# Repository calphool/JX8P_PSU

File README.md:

# JX8P_PSU
Replacement power supply for Roland JX8P

The power supply for the Roland JX8P is nearly 40 years old at this point, and if you own a JX8P you should probably be a little concerned about its 
typical manner of failing, which is to spike the +5V rail (your logic rail) frying lots of logic chips on your synth.  It is also built 
around heat generating linear regulators, which makes its demise even more likely.

I decided to replace mine preventatively, and this project is the result of that effort.  It's basically three Recom power modules with a common ground, and 
various conditioning components on the output side to make sure we have perfectly smooth rails, despite the fact that these are switching rather than linear 
supplies.  It works fabulously.

The LEDs and resistors near them are optional, but they give you an easy way to identify that all 4 rails are operating properly.  

Be aware that this 
PCB is managing mains voltages, so don't take on this project if you don't know what you're doing, or if this is a first attempt at building a PCB.  
**Don't fool with mains voltages unless you know precisely how to protect yourself.**

Also be aware that this PCB needs insulation on the bottom of the board.  The JX8P uses a shielded metal foil that is grounded.  You'll get fireworks if you 
just plunk this PCB down and connect it.  I used a sheet of plexiglass, and attached the board and plexiglass to the wooden base of the synth using 6-32 
nylon screws and nuts.

I sourced all the components from Mouser, though you can probably find them anywhere.  

The board has some safety features.  Since what we care about is the synth, I strapped all the rails to some very sturdy zeners that should protect the 
sensitive components of the synth if somehow one of the power units went out of spec.

The total current draw across the fuse is just above 1.5 amps, so a 2 amp fuse should probably be what you use.

I've included a Gerber .zip file, so you can just send the .zip to your favorite PCB fab house.

On the mains side (labeled N / L), you'll take the output of the JX8P's filter board, and connect it here.  Remove the transformer and the old power supply 
board.  The leads that used to go to the transformer (the green and the white) will now connect to this board.  The white one should connect to the N screw terminal and 
the green one should connect to the L screw terminal.

Regarding the connectors that go to the synthesizer itself, they are no longer available, so I desoldered the old ones from my old power supply board.  If 
you don't have good desoldering tools, you have other options.  You could snip the connector off of the synth and simply solder the wires directly, making sure to label 
them before you cut anything.  You could also change the connector to something more standard and user header pins, again be sure to label each wire before 
you do this.  The old power supply actually has markings for the voltages for each wire, and the wires are color coded as well.

At the time this was originally built (May 2025), you could get 5 PCBs from PCBWay for around $40, and the total cost for all the components is around $90, 
so for $130 you should be able to replace your old power supply, which is considerably cheaper than some so-called "professional" replacement power supplies 
I've seen online.  I seriously doubt that these "professional" boards are any more professional that this one, as all the heavy lifting is done in three 
components -- the Recom modules.  I didn't try it, but you *might* literally be able to get away with doing nothing more than connecting your synth directly 
to the outputs of the three Recom modules (making sure that you combine their output grounds).  I chose to put components after the output to make sure it's 
smooth and without ripple, but those Recom modules might be sufficient without all that stuff.

Best of luck.  As always, this project is a personal project.  I am not liable for any damage you do to your synth, to yourself, your friends and family, or 
to your property, even if there is an error in this design.  Build at your own risk, and make sure to check the output voltages on everything before you connect it to your synth.

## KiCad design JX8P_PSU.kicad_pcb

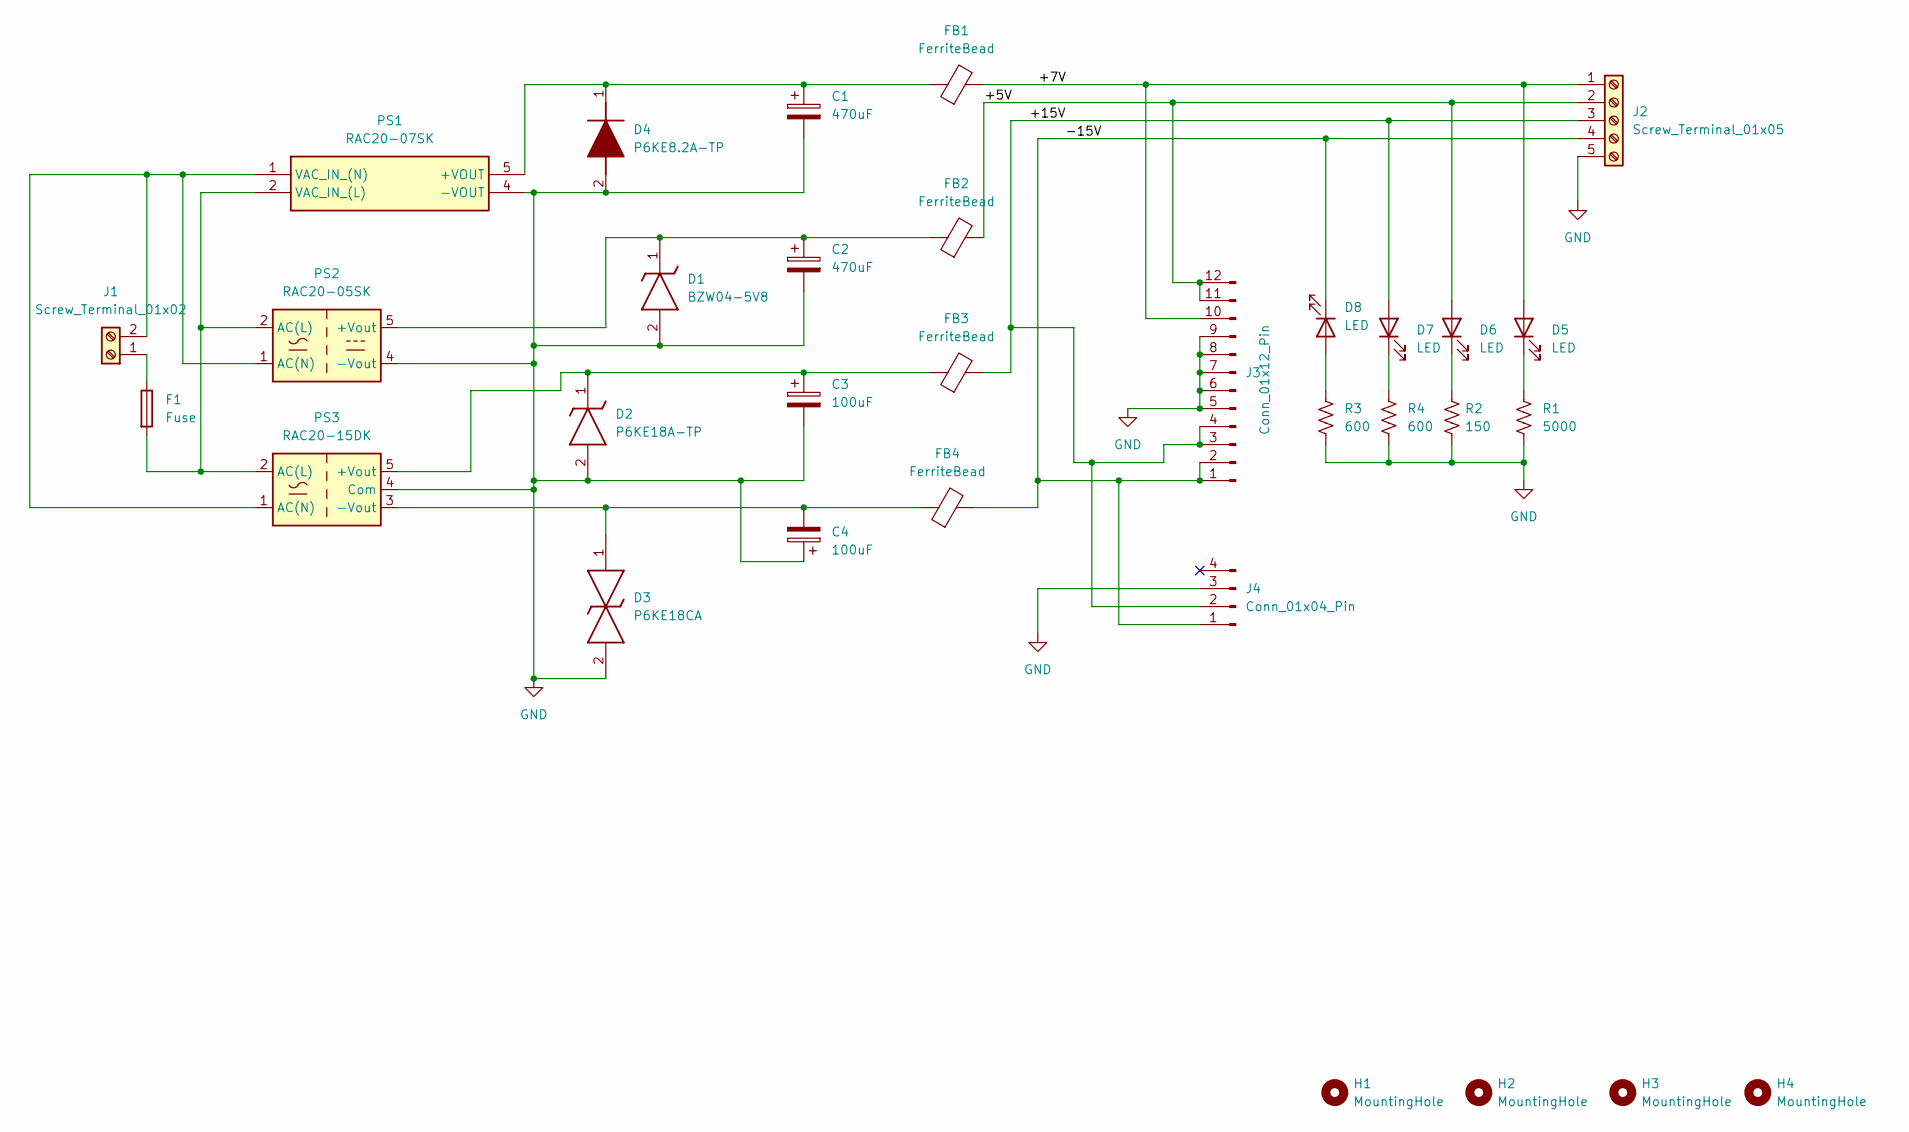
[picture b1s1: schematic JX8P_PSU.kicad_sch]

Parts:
C1, C2: 470uF; CP_Radial_D10.0mm_P2.50mm; Mouser Part Number 667-EEU-FR1V471
C3, C4: 100uF; CP_Radial_D10.0mm_P2.50mm; Mouser Part Number 667-EEU-FR1J101
D1: BZW04-5V8; D_5W_P12.70mm_Horizontal; Mouser Part Number 511-BZW04-5V8
D2: P6KE18A-TP; D_5W_P12.70mm_Horizontal; Mouser Part Number 833-P6KE18A-TP
D3: P6KE18CA; D_5W_P12.70mm_Horizontal; Mouser Part Number 511-P6KE18CA
D4: P6KE8.2A-TP; D_5W_P12.70mm_Horizontal; Mouser Part Number 833-P6KE8.2A-TP
D5: LED; LED_D3.0mm; Mouser Part Number 593-VAOL-3MSBY2
D6: LED; LED_D3.0mm; Mouser Part Number 859-LTL-4211N
D7: LED; LED_D3.0mm; Mouser Part Number 859-LTL-1CHG
D8: LED; LED_D3.0mm; Mouser Part Number 859-LTL-4251N
F1: Fuse; Fuseholder_Clip-6.3x32mm_Littelfuse_102_Inline_P34.21x7.62m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; Mouser Part Number 576-01020071Z
FB1, FB2, FB3, FB4: FerriteBead; LairdTech_28C0236-0JW-10; Mouser Part Number 875-28C0236-0JW-10
H1, H2, H3, H4: MountingHole; MountingHole_3.2mm_M3
J1: Screw_Terminal_01x02; TerminalBlock_Altech_AK300-2_P5.00mm; Mouser Part Number 845-30.602
J2: Screw_Terminal_01x05; Altech_AK100_1x05_P5.00mm; Mouser Part Number 179-TB0010-500-05GR
J3: Conn_01x12_Pin; Molex_KK-254_AE-6410-12A_1x12_P2.54mm_Vertical
J4: Conn_01x04_Pin; Molex_KK-254_AE-6410-04A_1x04_P2.54mm_Vertical
PS1: RAC20-07SK; Converter_ACDC_Recom_RAC20-xxSK_THT; Mouser Part Number 919-RAC20-07SK
PS2: RAC20-05SK; Converter_ACDC_Recom_RAC20-xxSK_THT; Mouser Part Number 919-RAC20-05SK
PS3: RAC20-15DK; Converter_ACDC_Recom_RAC20-xxDK_THT; Mouser Part Number 919-RAC20-15DK
R1: 5000; R_Axial_DIN0309_L9.0mm_D3.2mm_P12.70mm_Horizontal
R2: 150; R_Axial_DIN0309_L9.0mm_D3.2mm_P12.70mm_Horizontal
R3, R4: 600; R_Axial_DIN0309_L9.0mm_D3.2mm_P12.70mm_Horizontal

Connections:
/+5V: D6.2 (A), FB2.2, J2.2, J3.11, J3.12
/+7V: D5.2 (A), FB1.2, J2.1, J3.10
/+15V: D7.2 (A), FB3.2, J2.3, J3.3, J3.4, J4.2
/-15V: D8.1 (K), FB4.2, J2.4, J3.1, J3.2, J4.1
GND: C1.2, C2.2, C3.2, C4.1, D1.2 (A), D2.2 (A), D3.2, D4.2 (A), J2.5, J3.5, J3.6, J3.7, J3.8, J3.9, J4.3, PS1.4 (-VOUT), PS2.4 (-Vout), PS3.4 (Com), R1.2, R2.2, R3.2, R4.2
unnamed: C2.1, D1.1 (K), FB2.1, PS2.5 (+Vout)
unnamed: C3.1, D2.1 (K), FB3.1, PS3.5 (+Vout)
unnamed: C1.1, D4.1 (K), FB1.1, PS1.5 (+VOUT)
unnamed: D5.1 (K), R1.1
unnamed: D6.1 (K), R2.1
unnamed: D7.1 (K), R4.1
unnamed: D8.2 (A), R3.1
unnamed: F1.1, J1.1
unnamed: J1.2, PS1.1 (VAC_IN_(N)), PS2.1 (AC(N)), PS3.1 (AC(N))
unnamed: F1.2, PS1.2 (VAC_IN_(L)), PS2.2 (AC(L)), PS3.2 (AC(L))
unnamed: C4.2, D3.1, FB4.1, PS3.3 (-Vout)

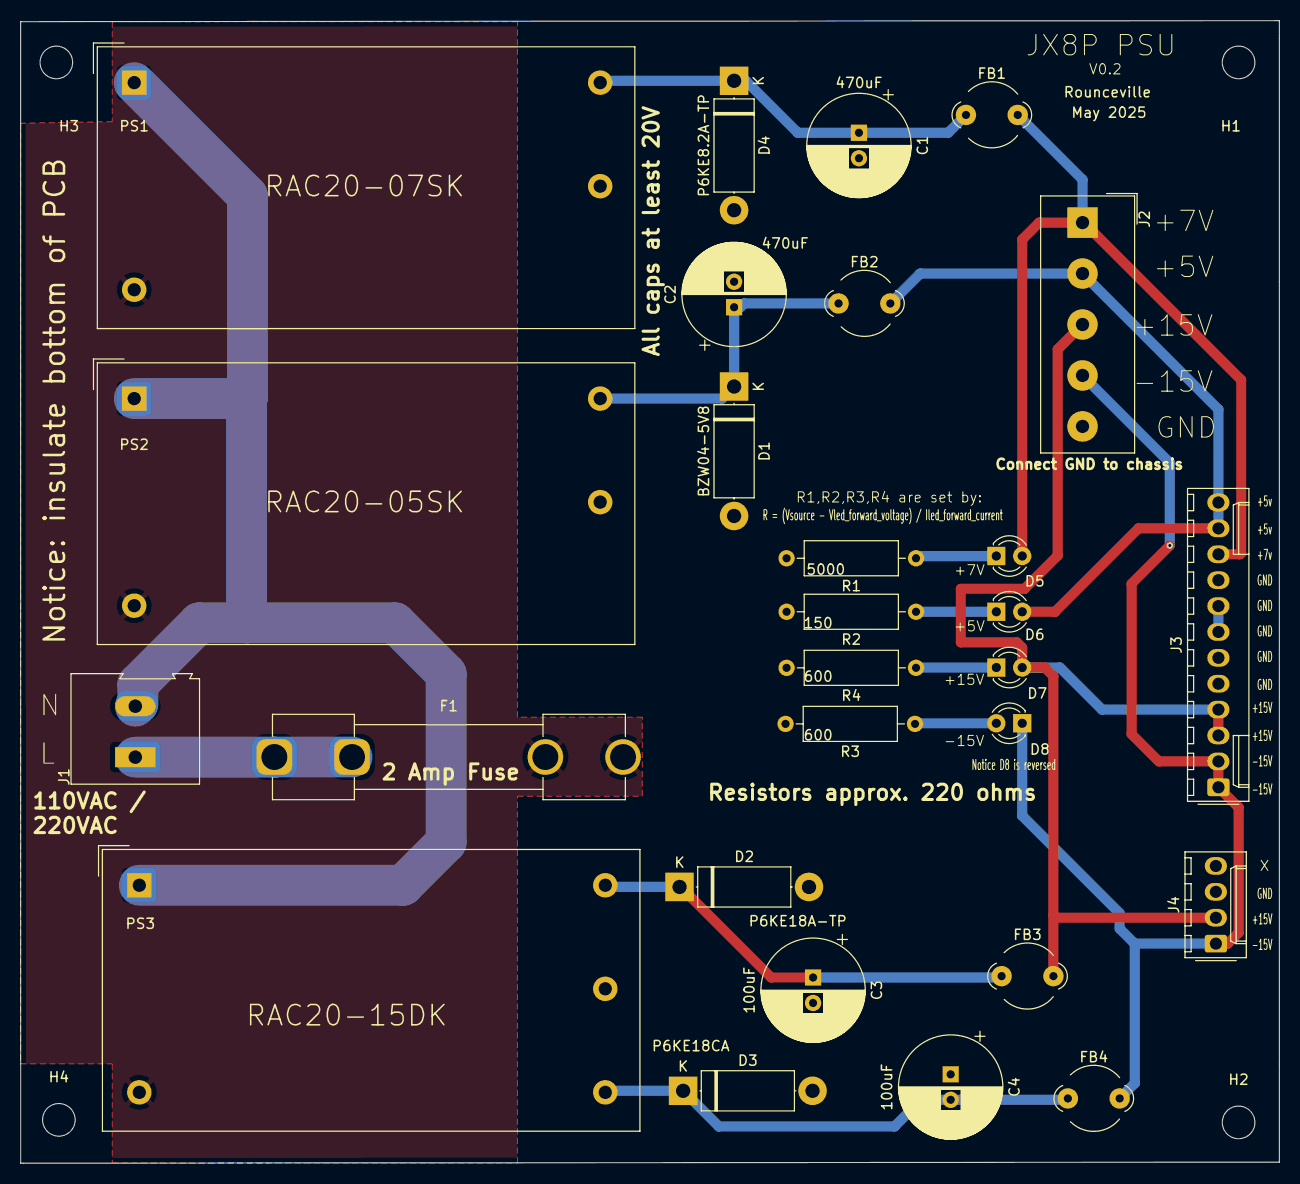
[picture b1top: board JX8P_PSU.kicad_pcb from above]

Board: 2 copper layers, 123.5 x 112.1 mm, 32 parts (0 on the bottom side), 16 nets.

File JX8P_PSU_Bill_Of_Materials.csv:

"Reference","Qty","Value","DNP","Exclude from BOM","Exclude from Board","Mouser Part Number"
"C1,C2","2","470uF","","","","667-EEU-FR1V471"
"C3,C4","2","100uF","","","","667-EEU-FR1J101"
"D1","1","BZW04-5V8","","","","511-BZW04-5V8"
"D2","1","P6KE18A-TP","","","","833-P6KE18A-TP"
"D3","1","P6KE18CA","","","","511-P6KE18CA"
"D4","1","P6KE8.2A-TP","","","","833-P6KE8.2A-TP"
"D5,D6,D7,D8","4","LED","","","","593-VAOL-3MSBY2,859-LTL-1CHG,859-LTL-4211N,859-LTL-4251N"
"F1","1","Fuse","","","","576-01020071Z"
"FB1,FB2,FB3,FB4","4","FerriteBead","","","","875-28C0236-0JW-10"
"H1,H2,H3,H4","4","MountingHole","","Excluded from BOM","",""
"J1","1","Screw_Terminal_01x02","","","","845-30.602"
"J2","1","Screw_Terminal_01x05","","","","179-TB0010-500-05GR"
"J3","1","Conn_01x12_Pin","","","",""
"J4","1","Conn_01x04_Pin","","","",""
"PS1","1","RAC20-07SK","","","","919-RAC20-07SK"
"PS2","1","RAC20-05SK","","","","919-RAC20-05SK"
"PS3","1","RAC20-15DK","","","","919-RAC20-15DK"
"R1","1","5000","","","",""
"R2","1","150","","","",""
"R3,R4","2","600","","","",""

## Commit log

2025-05-22 initial upload
2025-05-22 renamed BOM file
2025-05-22 added readme for gerbers
2025-05-22 fixed readme
2025-05-22 minor changes
